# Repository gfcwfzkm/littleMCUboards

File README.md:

# littleMCUboards
A collection of my little dev boards, that I develop and make to explore a new controller. These little microcontroller boards are made to fit into a specific socket of a main-devboard system, at which additional peripherals (Displays, Buttons & Switches, LED-Boards etc.) can be connected to.

The latest and future mcu boards feature a USB-C port for power and self-programming capabilities, either via a bootloader and a USB-to-Serial converter, or straight to the controller's USB-Ports. Also feature the pins brought out for a JTAG, SWD or other kind of programmer.

With this these boards themself can be used alone without the main-devboard system. Old boards that miss that will be uploaded in the /legacy/ folder.

Boards will be uploaded in the following days, so stay tuned!

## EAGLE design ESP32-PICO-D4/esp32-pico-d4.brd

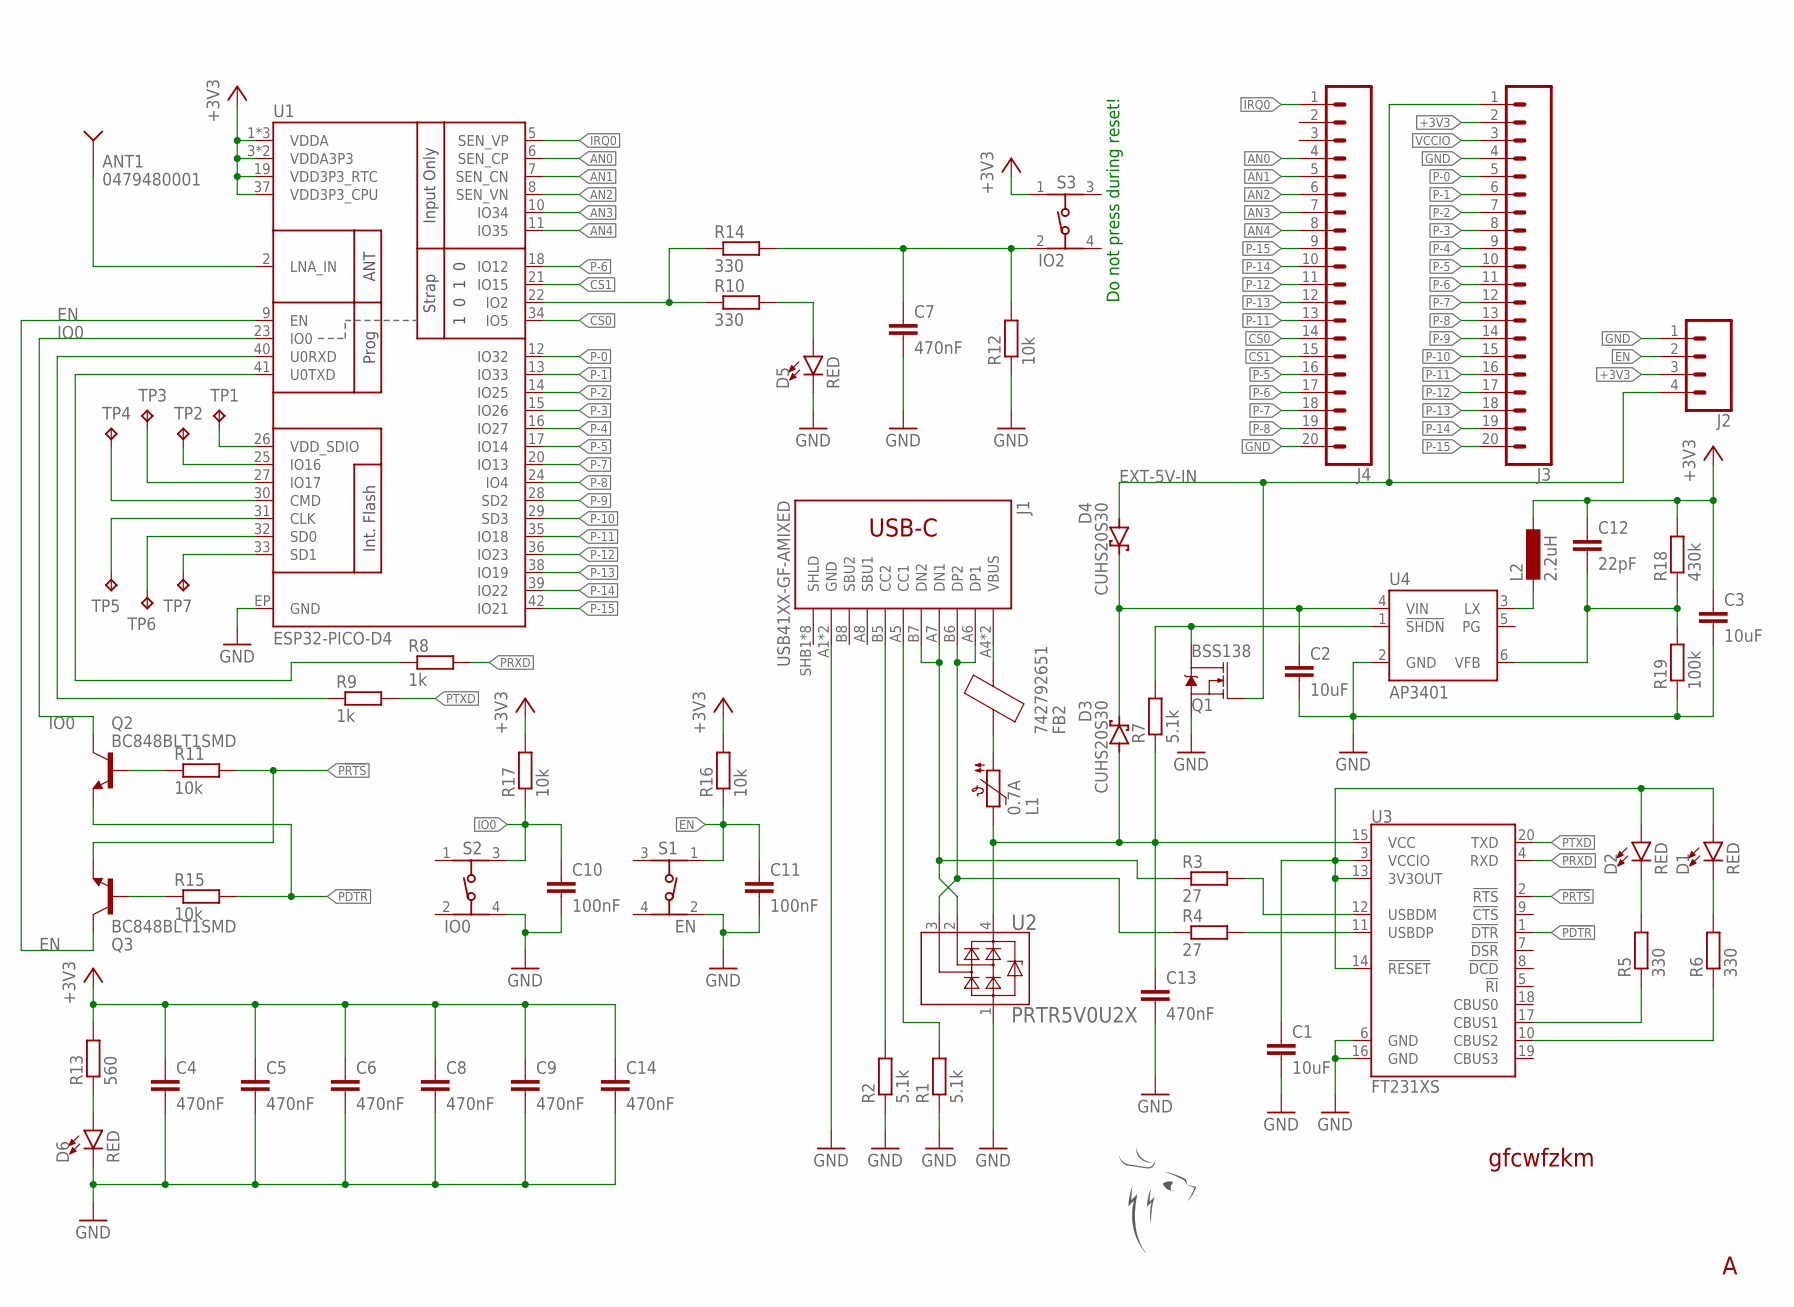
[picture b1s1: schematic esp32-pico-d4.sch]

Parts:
ANT1: 0479480001; RFANT2.4G_MOLEX_0479480001
C1, C2, C3: 10uF; C0603
C4, C5, C6, C7, C8, C9, C13, C14: 470nF; C0603
C10, C11: 100nF; C0603
C12: 22pF; C0603
D1, D2, D5, D6: RED; LED-0603
D3, D4: CUHS20S30; US2H
FB2: 742792651; R0603
J1: USB41XX-GF-AMIXED; USB4105-GF-A
J2: CONN_04; 1X04
J3, J4: CONN_20; 1X20
L1: 0.7A; R0805
L2: 2.2uH; R0805
Q1: BSS138; SOT23-3
Q2, Q3: BC848BLT1SMD; SOT23
R1, R2, R7: 5.1k; R0603
R3, R4: 27; R0603
R5, R6, R10, R14: 330; R0603
R8, R9: 1k; R0603
R11, R12, R15, R16, R17: 10k; R0603
R13: 560; R0603
R18: 430k; R0603
R19: 100k; R0603
S1: EN; 434153017835
S2: IO0; 434153017835
S3: IO2; 434153017835
TP1, TP2, TP3, TP4, TP5, TP6, TP7: TPB1,27; B1,27
U1: ESP32-PICO-D4; QFN-48-ESP32
U2: PRTR5V0U2X; SOT143B
U3: FT231XS; SSOP20_L
U4: AP3401; TSOT23-6
U$1: LOGO_PASCAL_GESELL10MM; LOGO_10MM

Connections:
!SHDN: Q1.3 (D), R7.2, U4.1 (!SHDN)
+3V3: C3.1, C4.1, C5.1, C6.1, C8.1, C9.1, C12.1, C14.1, J2.3, J3.2, L2.1, R13.2, R16.2, R17.2, R18.2, S3.1, U1.1 (VDDA), U1.3 (VDDA3P3), U1.4 (VDDA3P3), U1.19 (VDD3P3_RTC), U1.37 (VDD3P3_CPU), U1.43 (VDDA), U1.46 (VDDA)
AN0: J4.4, U1.6 (SEN_CP)
AN1: J4.5, U1.7 (SEN_CN)
AN2: J4.6, U1.8 (SEN_VN)
AN3: J4.7, U1.10 (IO34)
AN4: J4.8, U1.11 (IO35)
CS0: J4.14, U1.34 (IO5)
CS1: J4.15, U1.21 (IO15)
EN: C11.1, J2.2, Q3.3 (C), R16.1, S1.1, U1.9 (EN)
EXT-5V-IN: D4.A, J2.4, J3.1, Q1.1 (G)
GND: C1.2, C2.2, C3.2, C4.2, C5.2, C6.2, C7.2, C8.2, C9.2, C10.2, C11.2, C13.2, C14.2, D5.C, D6.C, J1.A1 (GND), J1.B1 (GND), J2.1, J3.4, J4.20, Q1.2 (S), R1.1, R2.1, R12.1, R19.1, S1.2 (3), S2.4, U1.EP (GND), U2.1, U3.6 (GND), U3.16 (GND), U4.2 (GND)
IO0: C10.1, Q2.3 (C), R17.1, S2.3 (2), U1.23 (IO0)
IRQ0: J4.1, U1.5 (SEN_VP)
LEDBTN: R10.1, R14.1, U1.22 (IO2)
LX: L2.2, U4.3 (LX)
unnamed: ANT1.RF, U1.2 (LNA_IN)
unnamed: J1.B5 (CC2), R2.2
unnamed: J1.A5 (CC1), R1.2
unnamed: C13.1, D3.A, L1.2, R7.1, U2.4, U3.15 (VCC)
unnamed: FB2.1, L1.1
unnamed: J1.A6 (DP1), J1.B6 (DP2), R4.1, U2.3
unnamed: J1.A7 (DN1), J1.B7 (DN2), R3.1, U2.2
unnamed: R4.2, U3.11 (USBDP)
unnamed: C1.1, D1.A, D2.A, U3.3 (VCCIO), U3.13 (3V3OUT), U3.14 (!RESET)
unnamed: R3.2, U3.12 (USBDM)
unnamed: D2.C, R5.2
unnamed: D1.C, R6.2
unnamed: R5.1, U3.17 (CBUS1)
unnamed: R6.1, U3.10 (CBUS2)
unnamed: R8.1, U1.41 (U0TXD)
unnamed: R9.1, U1.40 (U0RXD)
unnamed: Q3.1 (B), R15.1
unnamed: D5.A, R10.2
unnamed: C7.1, R12.2, R14.2, S3.2 (3)
unnamed: D6.A, R13.1
unnamed: Q2.1 (B), R11.1
unnamed: TP1.TP, U1.26 (VDD_SDIO)
unnamed: TP2.TP, U1.25 (IO16)
unnamed: TP3.TP, U1.27 (IO17)
unnamed: TP4.TP, U1.30 (CMD)
unnamed: TP7.TP, U1.33 (SD1)
unnamed: TP6.TP, U1.32 (SD0)
unnamed: TP5.TP, U1.31 (CLK)
P!DTR: Q2.2 (E), R15.2, U3.1 (!DTR)
P!RTS: Q3.2 (E), R11.2, U3.2 (!RTS)
P-0: J3.5, U1.12 (IO32)
P-1: J3.6, U1.13 (IO33)
P-2: J3.7, U1.14 (IO25)
P-3: J3.8, U1.15 (IO26)
P-4: J3.9, U1.16 (IO27)
P-5: J3.10, J4.16, U1.17 (IO14)
P-6: J3.11, J4.17, U1.18 (IO12)
P-7: J3.12, J4.18, U1.20 (IO13)
P-8: J3.13, J4.19, U1.24 (IO4)
P-9: J3.14, U1.28 (SD2)
P-10: J3.15, U1.29 (SD3)
P-11: J3.16, J4.13, U1.35 (IO18)
P-12: J3.17, J4.11, U1.36 (IO23)
P-13: J3.18, J4.12, U1.38 (IO19)
P-14: J3.19, J4.10, U1.39 (IO22)
P-15: J3.20, J4.9, U1.42 (IO21)
PRXD: R8.2, U3.4 (RXD)
PTXD: R9.2, U3.20 (TXD)
VBUS: FB2.2, J1.A4 (VBUS), J1.B4 (VBUS)
VCCIO: J3.3
VFB: C12.2, R18.1, R19.2, U4.6 (VFB)
VIN: C2.1, D3.C, D4.C, U4.4 (VIN)

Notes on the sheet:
Do not press during reset!
gfcwfzkm

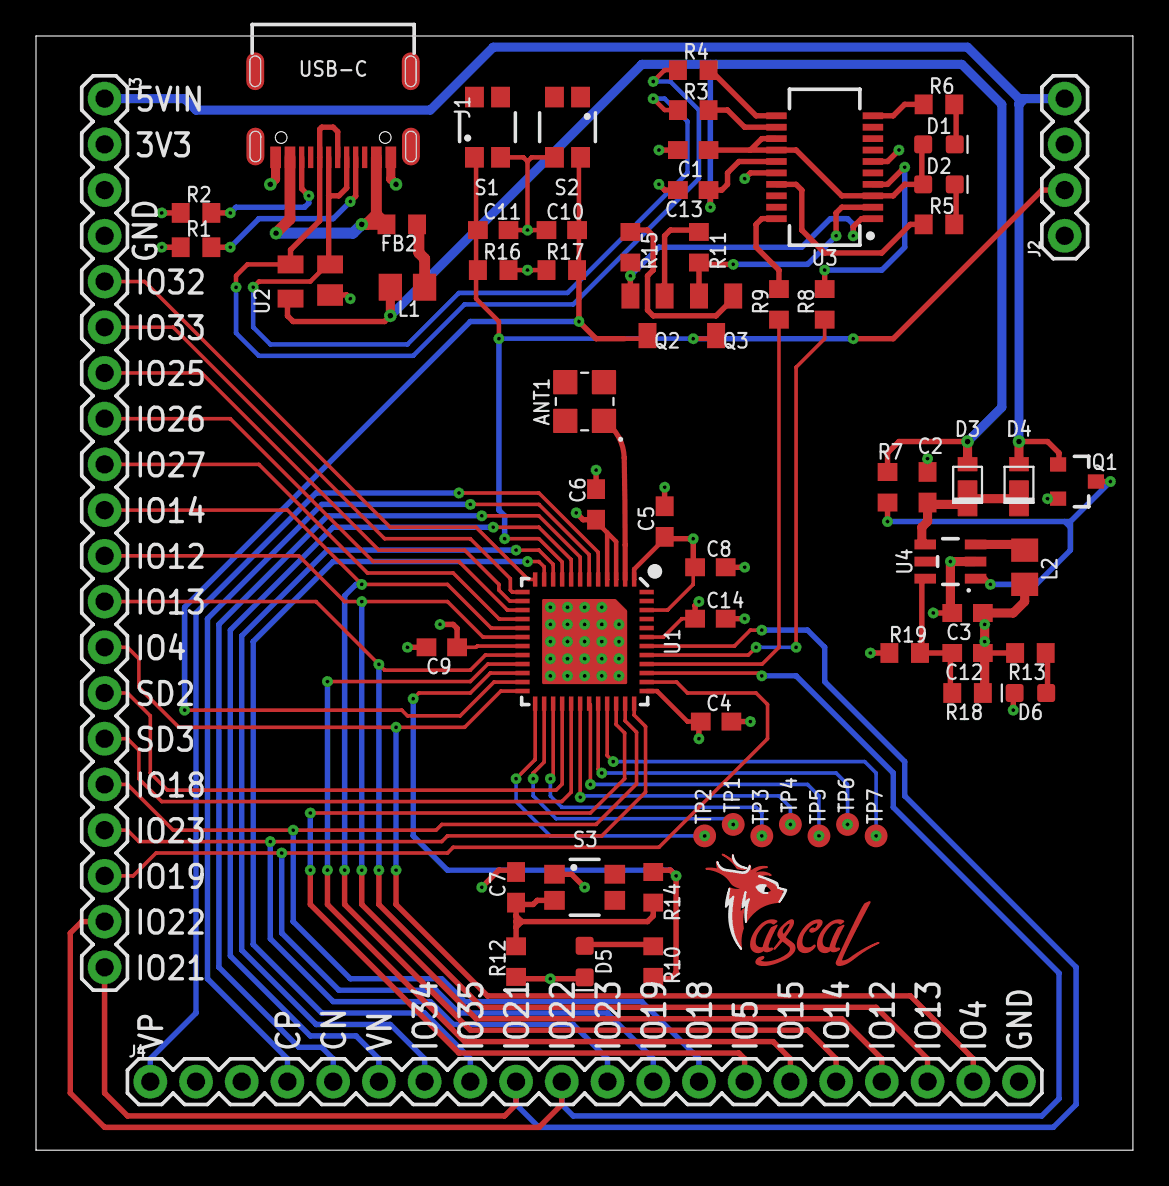
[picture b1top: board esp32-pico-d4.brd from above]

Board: 4 copper layers, 60.9 x 61.9 mm, 65 parts (0 on the bottom side), 67 nets.

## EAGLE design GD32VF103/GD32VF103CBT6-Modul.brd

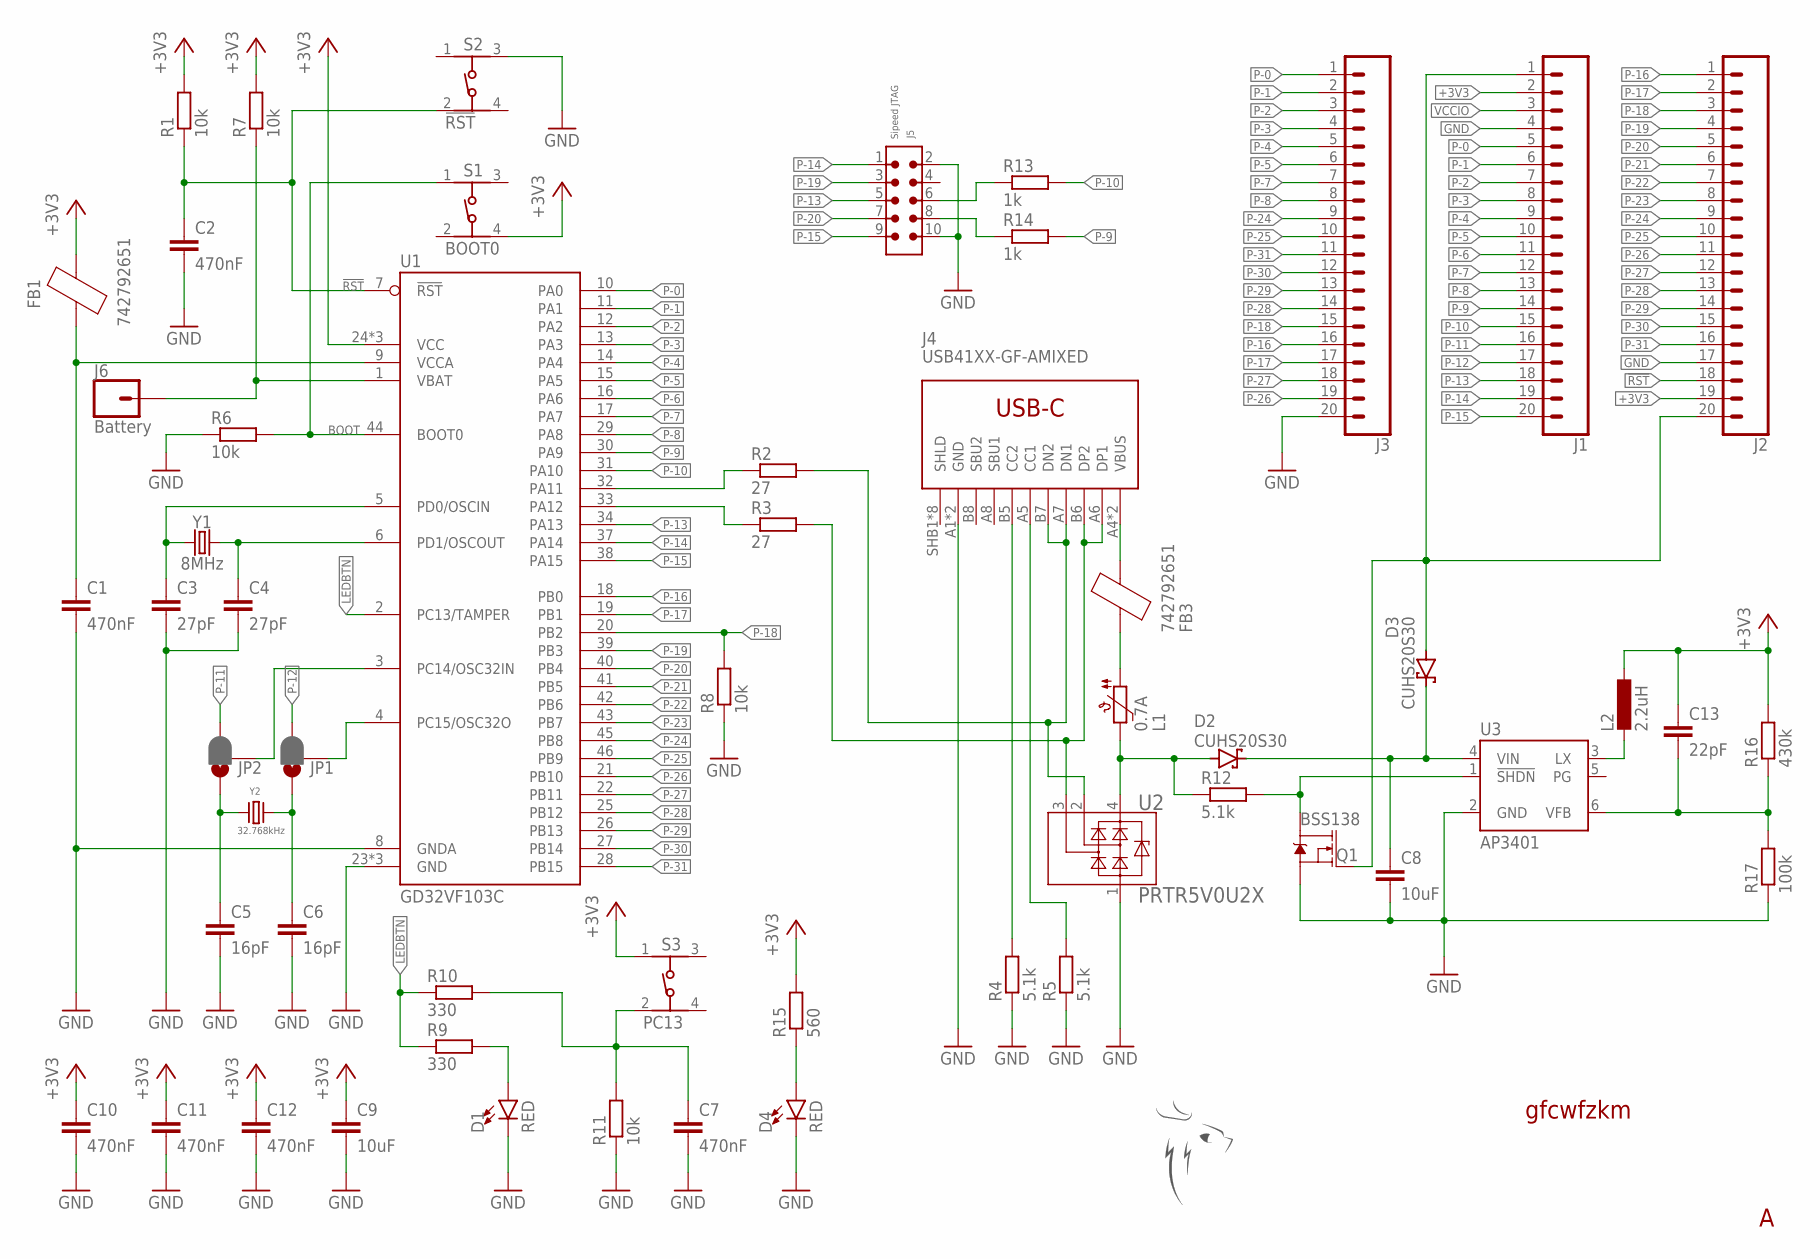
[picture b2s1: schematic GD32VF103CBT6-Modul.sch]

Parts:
C1, C2, C7, C10, C11, C12: 470nF; C0603
C3, C4: 27pF; C0603
C5, C6: 16pF; C0603
C8, C9: 10uF; C0603
C13: 22pF; C0603
D1, D4: RED; LED-0603
D2, D3: CUHS20S30; US2H
FB1, FB3: 742792651; R0603
J1, J2, J3: CONN_20; 1X20
J4: USB41XX-GF-AMIXED; USB4105-GF-A
J5: Sipeed JTAG; 61201021621
J6: Battery; 1X01
JP1, JP2: JUMPER-SMT_3_1-NC_PASTE_SILK; SMT-JUMPER_3_1-NC_PASTE_SILK
L1: 0.7A; R0805
L2: 2.2uH; R1210
Q1: BSS138; SOT23-3
R1, R6, R7, R8, R11: 10k; R0603
R2, R3: 27; R0603
R4, R5, R12: 5.1k; R0603
R9, R10: 330; R0603
R13, R14: 1k; R0603
R15: 560; R0603
R16: 430k; R0603
R17: 100k; R0603
S1: BOOT0; 434153017835
S2: !RST; 434153017835
S3: PC13; 434153017835
U1: GD32VF103C; LQFP48
U2: PRTR5V0U2X; SOT143B
U3: AP3401; TSOT23-6
U$1: LOGO_PASCAL_GESELL10MM; LOGO_10MM
Y1: 8MHz; CRYSTAL-SMD-5X3.2-4PAD
Y2: 32.768kHz; WE-XTAL_CFPX-56

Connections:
!RST: C2.1, J2.18, R1.1, S2.2 (3), U1.7 (!RST)
!SHDN: Q1.3 (D), R12.2, U3.1 (!SHDN)
+3V3: C9.1, C10.1, C11.1, C12.1, C13.1, FB1.2, J1.2, J2.19, L2.1, R1.2, R7.2, R15.2, R16.2, S1.4, S3.1, U1.24 (VCC), U1.36 (VCC), U1.48 (VCC)
BOOT: R6.2, S1.1, U1.44 (BOOT0)
D+: J4.A6 (DP1), J4.B6 (DP2), R3.2, U2.3
D-: J4.A7 (DN1), J4.B7 (DN2), R2.2, U2.2
GND: C1.2, C2.2, C3.2, C4.2, C5.2, C6.2, C7.2, C8.2, C9.2, C10.2, C11.2, C12.2, D1.C, D4.C, J1.4, J2.17, J3.20, J4.A1 (GND), J4.B1 (GND), J5.2, J5.10, Q1.2 (S), R4.1, R5.1, R6.1, R8.1, R11.1, R17.1, S2.3 (2), U1.8 (GNDA), U1.23 (GND), U1.35 (GND), U1.47 (GND), U2.1, U3.2 (GND)
LEDBTN: R9.1, R10.1, U1.2 (PC13/TAMPER)
LX: L2.2, U3.3 (LX)
unnamed: C3.1, U1.5 (PD0/OSCIN), Y1.1
unnamed: C4.1, U1.6 (PD1/OSCOUT), Y1.3 (2)
unnamed: JP2.2, U1.3 (PC14/OSC32IN)
unnamed: JP1.2, U1.4 (PC15/OSC32O)
unnamed: R2.1, U1.32 (PA11)
unnamed: R3.1, U1.33 (PA12)
unnamed: J4.B5 (CC2), R4.2
unnamed: J4.A5 (CC1), R5.2
unnamed: FB3.1, L1.1
unnamed: D2.A, L1.2, R12.1, U2.4
unnamed: C6.1, JP1.1, Y2.2
unnamed: C5.1, JP2.1, Y2.1
unnamed: C1.1, FB1.1, U1.9 (VCCA)
unnamed: C7.1, R10.2, R11.2, S3.2 (3)
unnamed: D1.A, R9.2
unnamed: J6.1, R7.1, U1.1 (VBAT)
unnamed: D3.A, J1.1, J2.20, Q1.1 (G)
unnamed: J5.6, R13.1
unnamed: J5.8, R14.1
unnamed: D4.A, R15.1
P-0: J1.5, J3.1, U1.10 (PA0)
P-1: J1.6, J3.2, U1.11 (PA1)
P-2: J1.7, J3.3, U1.12 (PA2)
P-3: J1.8, J3.4, U1.13 (PA3)
P-4: J1.9, J3.5, U1.14 (PA4)
P-5: J1.10, J3.6, U1.15 (PA5)
P-6: J1.11, U1.16 (PA6)
P-7: J1.12, J3.7, U1.17 (PA7)
P-8: J1.13, J3.8, U1.29 (PA8)
P-9: J1.14, R14.2, U1.30 (PA9)
P-10: J1.15, R13.2, U1.31 (PA10)
P-11: J1.16, JP2.3
P-12: J1.17, JP1.3
P-13: J1.18, J5.5, U1.34 (PA13)
P-14: J1.19, J5.1, U1.37 (PA14)
P-15: J1.20, J5.9, U1.38 (PA15)
P-16: J2.1, J3.16, U1.18 (PB0)
P-17: J2.2, J3.17, U1.19 (PB1)
P-18: J2.3, J3.15, R8.2, U1.20 (PB2)
P-19: J2.4, J5.3, U1.39 (PB3)
P-20: J2.5, J5.7, U1.40 (PB4)
P-21: J2.6, U1.41 (PB5)
P-22: J2.7, U1.42 (PB6)
P-23: J2.8, U1.43 (PB7)
P-24: J2.9, J3.9, U1.45 (PB8)
P-25: J2.10, J3.10, U1.46 (PB9)
P-26: J2.11, J3.19, U1.21 (PB10)
P-27: J2.12, J3.18, U1.22 (PB11)
P-28: J2.13, J3.14, U1.25 (PB12)
P-29: J2.14, J3.13, U1.26 (PB13)
P-30: J2.15, J3.12, U1.27 (PB14)
P-31: J2.16, J3.11, U1.28 (PB15)
VBUS: FB3.2, J4.A4 (VBUS), J4.B4 (VBUS)
VCCIO: J1.3
VFB: C13.2, R16.1, R17.2, U3.6 (VFB)
VIN: C8.1, D2.C, D3.C, U3.4 (VIN)

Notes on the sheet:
gfcwfzkm

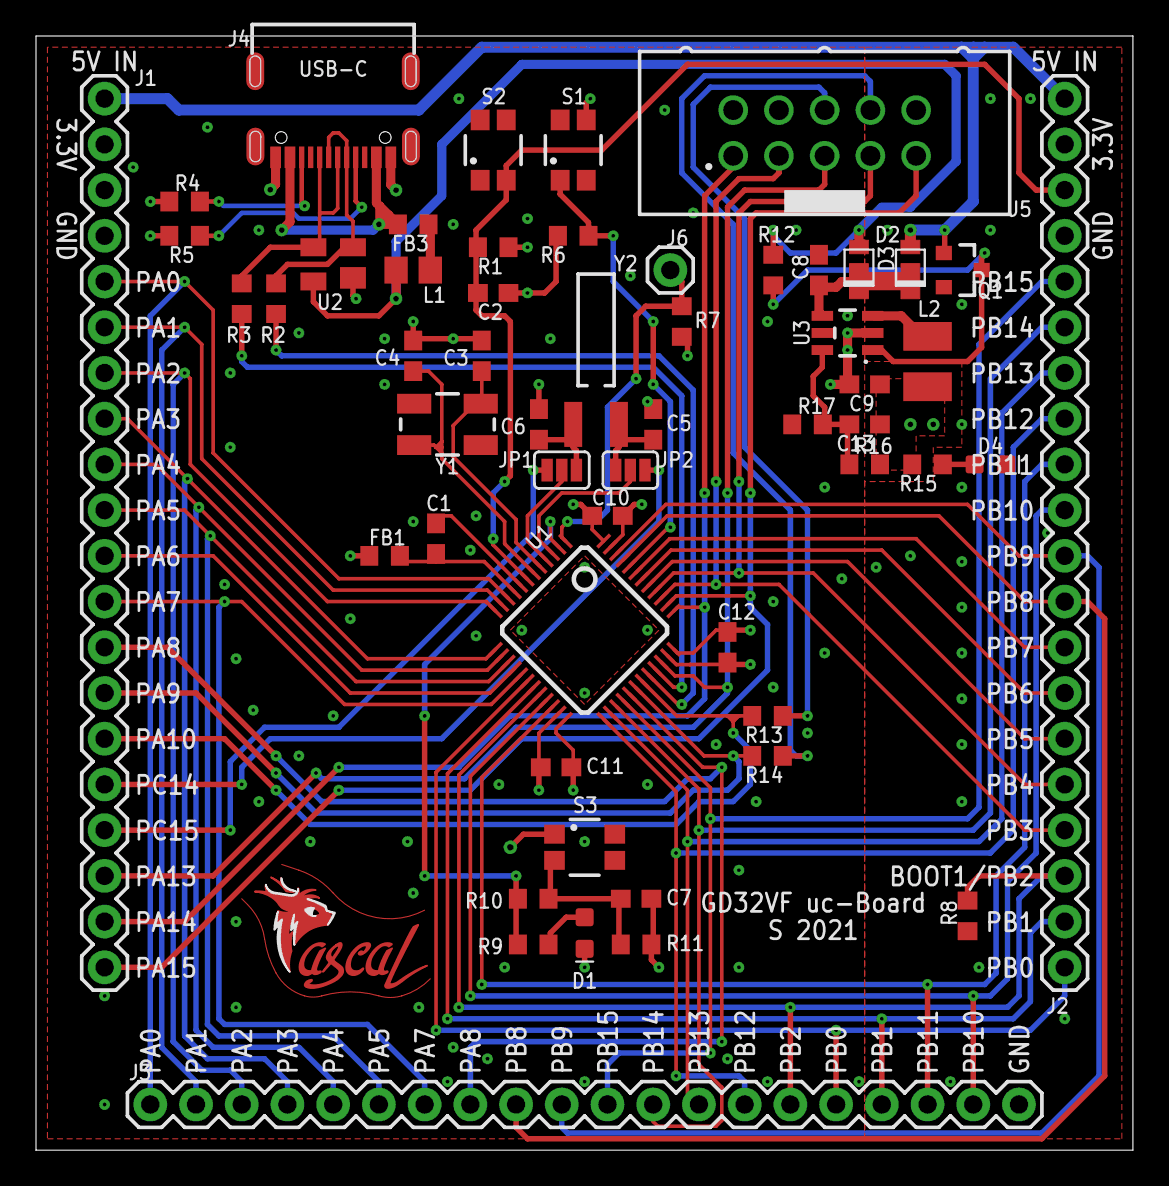
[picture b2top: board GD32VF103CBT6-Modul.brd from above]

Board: 4 copper layers, 60.9 x 61.9 mm, 56 parts (0 on the bottom side), 64 nets.

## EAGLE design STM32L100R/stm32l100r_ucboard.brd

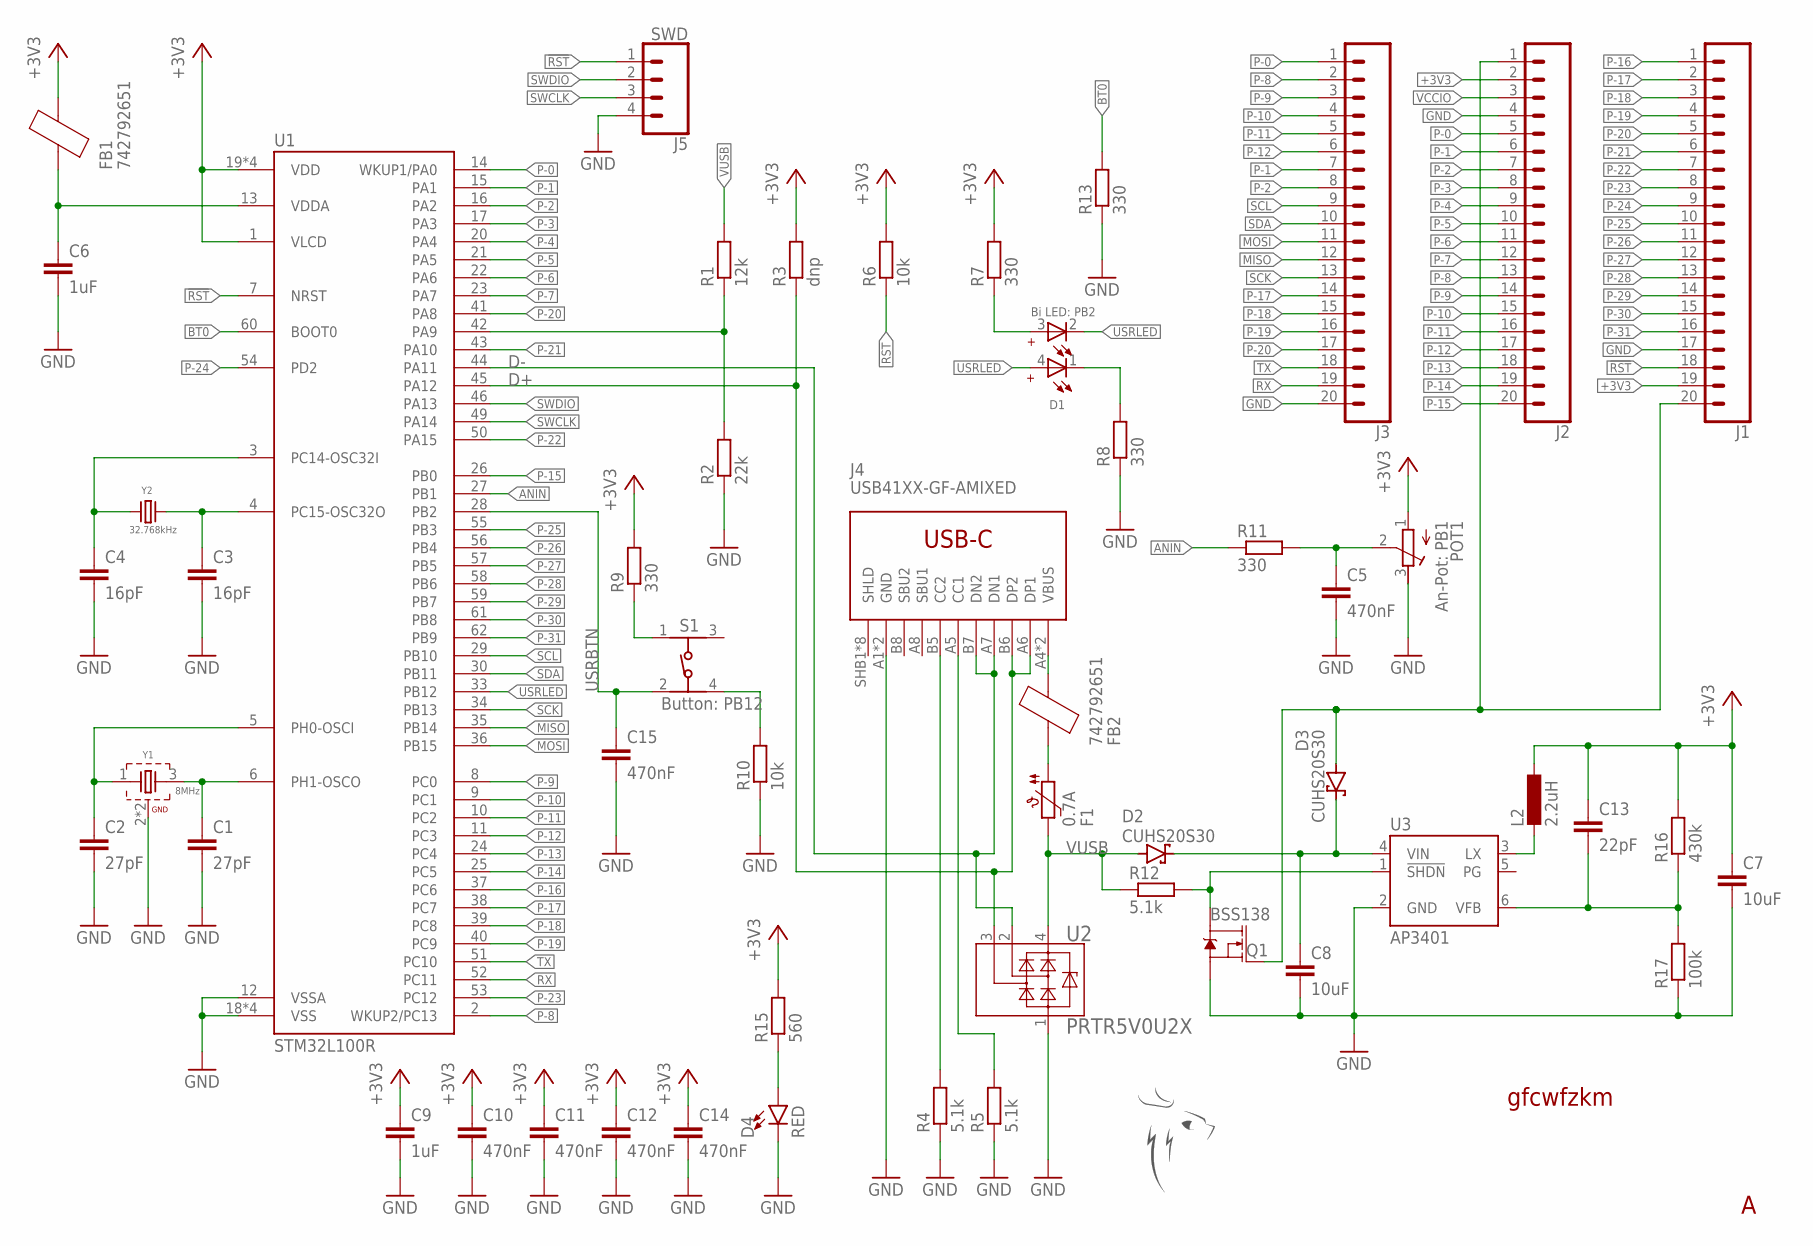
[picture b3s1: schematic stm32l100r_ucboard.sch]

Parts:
C1, C2: 27pF; C0603
C3, C4: 16pF; C0603
C5, C10, C11, C12, C14, C15: 470nF; C0603
C6, C9: 1uF; C0603
C7, C8: 10uF; C0603
C13: 22pF; C0603
D1: Bi LED: PB2; WL-SBCD_0805
D2, D3: CUHS20S30; US2H
D4: RED; LED-0603
F1: 0.7A; R0805
FB1, FB2: 742792651; R0603
J1, J2, J3: CONN_20; 1X20
J4: USB41XX-GF-AMIXED; USB4105-GF-A
J5: SWD; 1X04_LOCK
L2: 2.2uH; R1210
POT1: An-Pot: PB1; 3386P
Q1: BSS138; SOT23-3
R1: 12k; R0603
R2: 22k; R0603
R3: dnp; R0603
R4, R5, R12: 5.1k; R0603
R6, R10: 10k; R0603
R7, R8, R9, R11, R13: 330; R0603
R15: 560; R0603
R16: 430k; R0603
R17: 100k; R0603
S1: Button: PB12; 434153017835
U1: STM32L100R; LQFP-ST-64-2
U2: PRTR5V0U2X; SOT143B
U3: AP3401; TSOT23-6
U$1: LOGO_PASCAL_GESELL10MM; LOGO_10MM
Y1: 8MHz; WE-XTAL_CFPX-104
Y2: 32.768kHz; WE-XTAL_CFPX-56

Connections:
!RST: J1.18, J5.1, R6.1, U1.7 (NRST)
!SHDN: Q1.3 (D), R12.2, U3.1 (!SHDN)
+3V3: C7.1, C9.1, C10.1, C11.1, C12.1, C13.1, C14.1, FB1.2, J1.19, J2.2, L2.1, POT1.1 (A), R3.2, R6.2, R7.2, R9.2, R15.2, R16.2, U1.1 (VLCD), U1.19 (VDD), U1.32 (VDD), U1.48 (VDD), U1.64 (VDD)
ANIN: R11.1, U1.27 (PB1)
BT0: R13.2, U1.60 (BOOT0)
D+: J4.A6 (DP1), J4.B6 (DP2), R3.1, U1.45 (PA12), U2.3
D-: J4.A7 (DN1), J4.B7 (DN2), U1.44 (PA11), U2.2
GND: C1.2, C2.2, C3.2, C4.2, C5.2, C6.2, C7.2, C8.2, C9.2, C10.2, C11.2, C12.2, C14.2, C15.2, D4.C, J1.17, J2.4, J3.20, J4.A1 (GND), J4.B1 (GND), J5.4, POT1.3 (E), Q1.2 (S), R2.1, R4.1, R5.1, R8.1, R10.1, R13.1, R17.1, U1.12 (VSSA), U1.18 (VSS), U1.31 (VSS), U1.47 (VSS), U1.63 (VSS), U2.1, U3.2 (GND), Y1.2 (GND), Y1.4 (GND)
LX: L2.2, U3.3 (LX)
MISO: J3.12, U1.35 (PB14)
MOSI: J3.11, U1.36 (PB15)
unnamed: C4.1, U1.3 (PC14-OSC32I), Y2.1
unnamed: C3.1, U1.4 (PC15-OSC32O), Y2.2
unnamed: C2.1, U1.5 (PH0-OSCI), Y1.1
unnamed: C1.1, U1.6 (PH1-OSCO), Y1.3 (2)
unnamed: C6.1, FB1.1, U1.13 (VDDA)
unnamed: D1.3 (G+), R7.1
unnamed: J4.B5 (CC2), R4.2
unnamed: J4.A5 (CC1), R5.2
unnamed: F1.1, FB2.1
unnamed: D1.1 (R-), R8.2
unnamed: R9.1, S1.1
unnamed: R10.2, S1.4
unnamed: C5.1, POT1.2 (S), R11.2
unnamed: D3.A, J1.20, J2.1, Q1.1 (G)
unnamed: R1.1, R2.2, U1.42 (PA9)
unnamed: D4.A, R15.1
P-0: J2.5, J3.1, U1.14 (WKUP1/PA0)
P-1: J2.6, J3.7, U1.15 (PA1)
P-2: J2.7, J3.8, U1.16 (PA2)
P-3: J2.8, U1.17 (PA3)
P-4: J2.9, U1.20 (PA4)
P-5: J2.10, U1.21 (PA5)
P-6: J2.11, U1.22 (PA6)
P-7: J2.12, U1.23 (PA7)
P-8: J2.13, J3.2, U1.2 (WKUP2/PC13)
P-9: J2.14, J3.3, U1.8 (PC0)
P-10: J2.15, J3.4, U1.9 (PC1)
P-11: J2.16, J3.5, U1.10 (PC2)
P-12: J2.17, J3.6, U1.11 (PC3)
P-13: J2.18, U1.24 (PC4)
P-14: J2.19, U1.25 (PC5)
P-15: J2.20, U1.26 (PB0)
P-16: J1.1, U1.37 (PC6)
P-17: J1.2, J3.14, U1.38 (PC7)
P-18: J1.3, J3.15, U1.39 (PC8)
P-19: J1.4, J3.16, U1.40 (PC9)
P-20: J1.5, J3.17, U1.41 (PA8)
P-21: J1.6, U1.43 (PA10)
P-22: J1.7, U1.50 (PA15)
P-23: J1.8, U1.53 (PC12)
P-24: J1.9, U1.54 (PD2)
P-25: J1.10, U1.55 (PB3)
P-26: J1.11, U1.56 (PB4)
P-27: J1.12, U1.57 (PB5)
P-28: J1.13, U1.58 (PB6)
P-29: J1.14, U1.59 (PB7)
P-30: J1.15, U1.61 (PB8)
P-31: J1.16, U1.62 (PB9)
RX: J3.19, U1.52 (PC11)
SCK: J3.13, U1.34 (PB13)
SCL: J3.9, U1.29 (PB10)
SDA: J3.10, U1.30 (PB11)
SWCLK: J5.3, U1.49 (PA14)
SWDIO: J5.2, U1.46 (PA13)
TX: J3.18, U1.51 (PC10)
USRBTN: C15.1, S1.2 (3), U1.28 (PB2)
USRLED: D1.2 (G-), D1.4 (R+), U1.33 (PB12)
VBUS: FB2.2, J4.A4 (VBUS), J4.B4 (VBUS)
VCCIO: J2.3
VFB: C13.2, R16.1, R17.2, U3.6 (VFB)
VIN: C8.1, D2.C, D3.C, U3.4 (VIN)
VUSB: D2.A, F1.2, R1.2, R12.1, U2.4

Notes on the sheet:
gfcwfzkm

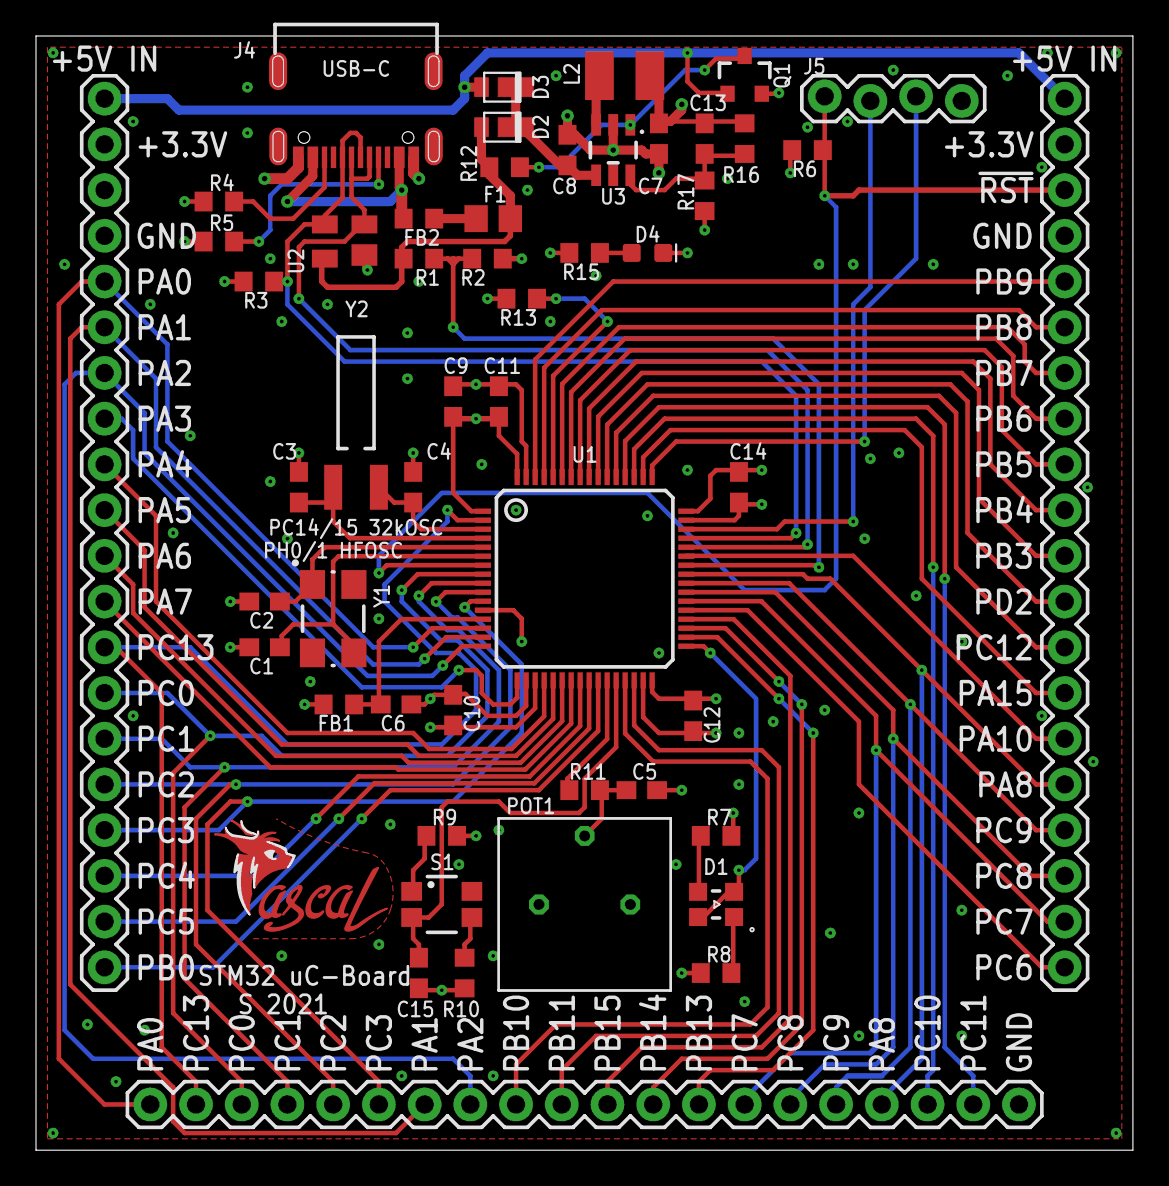
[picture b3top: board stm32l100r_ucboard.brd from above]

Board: 4 copper layers, 60.9 x 61.9 mm, 53 parts (0 on the bottom side), 72 nets.

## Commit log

2021-06-15 dump file to create folder
2021-06-15 dump file to create folder structure
2021-06-25 Initial upload

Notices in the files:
parts and their libraries:
SparkFun-LED: Licensing: Creative Commons ShareAlike 4.0 International - https://creativecommons.org/licenses/by-sa/4.0
Wurth_Switch_WS-TASV: Copyright: Würth Elektronik
